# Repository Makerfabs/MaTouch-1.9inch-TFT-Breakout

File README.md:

MaTouch 1.9“ TFT Breakout

```c++
/*
Version:		V1.1
Author:		Charlin
Create Date:	2023/8/14
Note:

*/
```

# Makerfabs

[Makerfabs home page](https://www.makerfabs.com/)

[Makerfabs Wiki](https://wiki.makerfabs.com/)

## Intruduce

Product Link:[MaTouch 1.9“ TFT Breakout](https://www.makerfabs.com/MaTouch-1.9-inch-TFT-Breakout.html)

Wiki Link : 

Makerfabs MaTouch 1.9” has got lots of interests, but we got many feedback that there the ESP32S3 pins should be breakout, for users’ application, so we designed this new board.

Compares to the old version, there main updates are the GPIO all been breakout, users can prototype it more easily with a breadboard, or use it as a “controller” for other boards by inserting it to other boards.

## Features

Specs:
- Controller: ESP32-S3
- Wireless: WiFi& Bluetooth 5.0
- LCD: 1.9", 320x170 resolution, driver ST7789V2
- LCD interface: 8 bit 8080
- Touch Panel Driver: CST816D
- USB: USB Native, Type-C
- Power Supply: USB Type-C 5.0V(4.0V~5.25V); 3.7V Lipo battery
- Button: Flash button and reset button
- MicroSD: Yes
- Arduino support: Yes
- MicroPython support: Yes
- Operation temperature: -40℃ to +85℃

# Usage

## Libraries

Related library versions

- Use type-c use cable connect USB-TTL to PC.
- Select "ESP32-S3 DEV Module"
- Select PSRAM "OPI PSRAM"

"mf_Lvgl" library is modified from Lvgl library (version 8.3.2). 

Please unzip "lib/mf_Lvgl.zip"."TouchLib" and copy to arduino library directory.

## Example

### firmware

Factory test program

### squareline_demo

SquareLine demo, connected DHT11 sensor, button, LED.

[Youtube](https://www.youtube.com/watch?v=VayIuLey8po&t=3s)

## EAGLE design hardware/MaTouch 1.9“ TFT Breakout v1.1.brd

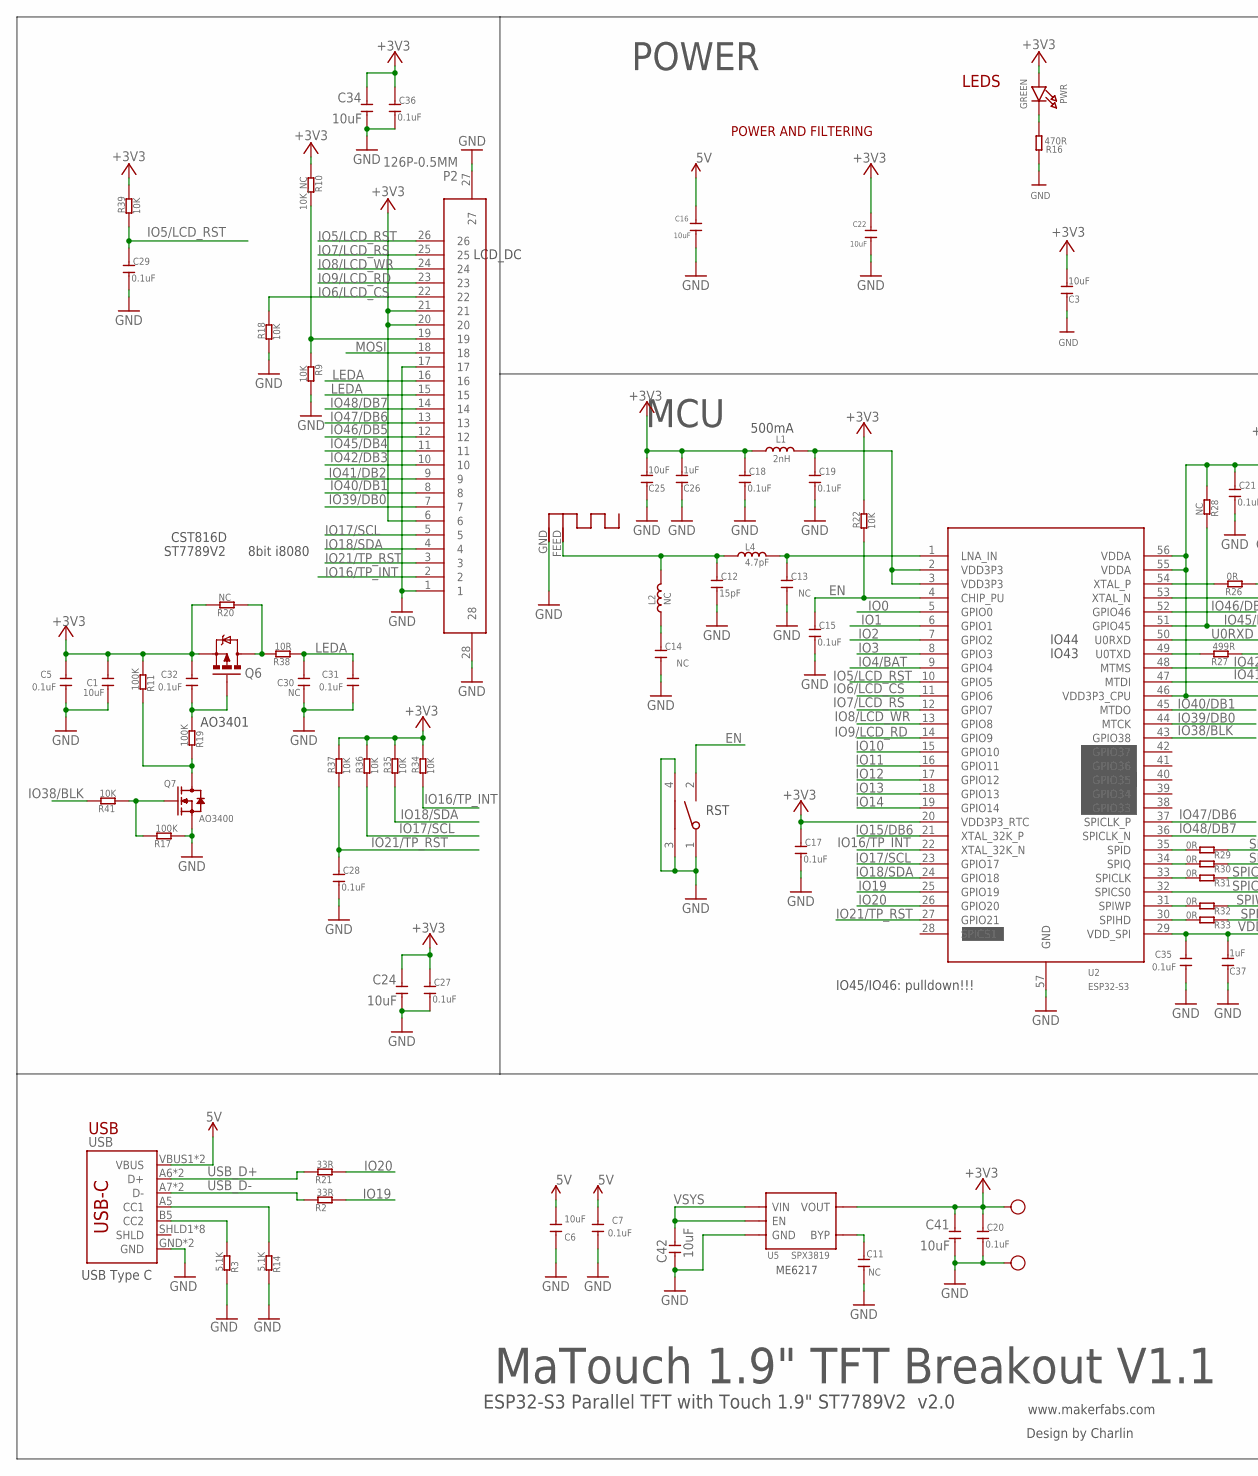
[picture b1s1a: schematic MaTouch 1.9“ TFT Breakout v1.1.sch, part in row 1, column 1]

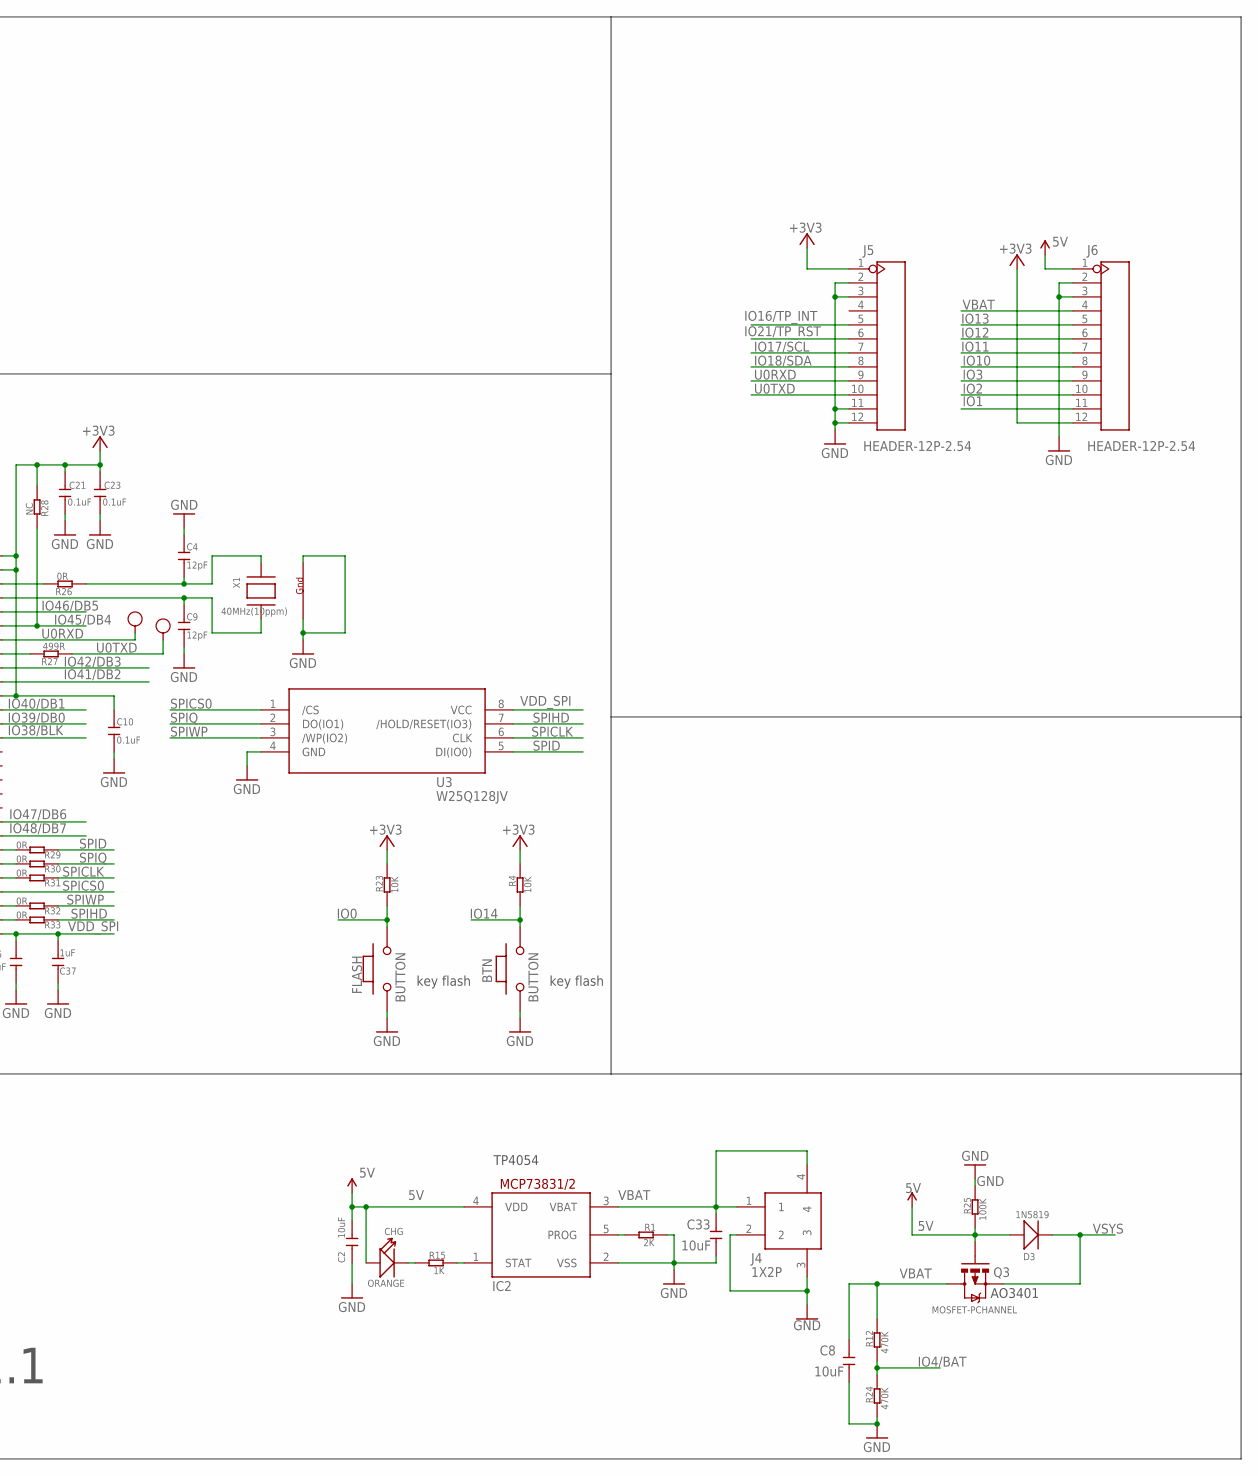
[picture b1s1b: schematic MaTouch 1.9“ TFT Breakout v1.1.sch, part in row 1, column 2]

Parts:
ANT1: ANTENNA; RN-ANT
BTN: BUTTON; 157SW
C1, C2, C8, C16, C22, C24, C33, C34, C41, C42: 10uF; 0603
C3, C6, C25: 10uF; DISCRETE_C0603
C4, C9: 12pF; DISCRETE_C0402
C5, C7, C10, C15, C17, C18, C19, C20, C21, C23, C27, C28, C29, C31, C32, C35, C36: 0.1uF; DISCRETE_C0402
C11, C13, C14: NC; DISCRETE_C0402
C12: 15pF; DISCRETE_C0402
C26, C37: 1uF; DISCRETE_C0603
C30: NC; 0603
CHG: ORANGE; D0603
D3: 1N5819; SOD323
FLASH: BUTTON; 157SW
G: TEST-POINT'4545'; TP-D45MIL; PARTNO DNP
IC2: MCP73831/OT; SOT23-5L
J4: 1X2P; 1X2P-SMT1.25MM
J5, J6: HEADER-12P-2.54; 12P-2.54
L1: 2nH; DISCRETE_L0603
L2: NC; DISCRETE_L0402
L4: 4.7pF; DISCRETE_L0402
P2: 126P-0.5MM; 1*26P-SMT0.5MM
PWR: GREEN; CHIPLED_0805_NOOUTLINE
Q3, Q6: MOSFET-PCHANNEL; SOT23-3
Q7: AO3400; DISCRETE_SOT23
R1: 2K; DISCRETE_R0402
R2, R21: 33R; DISCRETE_R0402
R3, R14: 5.1K; DISCRETE_R0402
R4, R9, R18, R22, R23, R34, R35, R36, R37, R39, R41: 10K; DISCRETE_R0402
R10: 10K_NC; DISCRETE_R0402
R11, R17, R19, R25: 100K; DISCRETE_R0402
R12, R24: 470K; DISCRETE_R0402
R15: 1K; DISCRETE_R0402
R16: 470R; DISCRETE_R0402
R20, R28: NC; DISCRETE_R0402
R26, R29, R30, R31, R32, R33: 0R; DISCRETE_R0402
R27: 499R; DISCRETE_R0402
R38: 10R; DISCRETE_R0402
RST: TS24CA; 2*4*3.5MM
RX: TEST-POINT'4545'; TP-D45MIL; PARTNO DNP
TX: TEST-POINT'4545'; TP-D45MIL; PARTNO DNP
U2: ESP32-S3; QFN56-7*7MM
U3: W25Q128JV; SOIC-8-208MIL
U5: SPX3819; SOT23-5
USB: USB_C5; USB-C-16P-5
V: TEST-POINT'4545'; TP-D45MIL; PARTNO DNP
X1: 40MHz(10ppm); NX3225

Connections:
5V: C2.2, C6.2, C7.2, C16.1, CHG.+, D3.+, IC2.4 (VDD), J6.1, Q3.1 (G), R25.1, USB.VBUS1 (VBUS), USB.VBUS2 (VBUS)
+3V3: C1.2, C3.2, C5.2, C10.2, C17.2, C18.2, C20.2, C21.2, C22.1, C23.2, C24.2, C25.2, C26.2, C27.2, C32.2, C34.2, C36.2, C41.2, J5.1, J6.12, L1.1, P2.6, P2.20, P2.21, PWR.A, Q6.2 (S), R4.2, R10.2, R11.1, R20.2, R22.2, R23.2, R28.1, R34.2, R35.2, R36.2, R37.2, R39.2, U2.20 (VDD3P3_RTC), U2.46 (VDD3P3_CPU), U2.55 (VDDA), U2.56 (VDDA), U5.5 (VOUT), V.T
EN: C15.2, R22.1, RST.2, U2.4 (CHIP_PU)
GND: ANT1.GND, BTN.1, C1.1, C2.1, C3.1, C4.2, C5.1, C6.1, C7.1, C8.1, C9.1, C10.1, C11.1, C12.1, C13.1, C14.1, C15.1, C16.2, C17.1, C18.1, C19.1, C20.1, C21.1, C22.2, C23.1, C24.1, C25.1, C26.1, C27.1, C28.1, C29.1, C30.1, C31.1, C33.1, C34.1, C35.1, C36.1, C37.1, C41.1, C42.1, FLASH.1, G.T, IC2.2 (VSS), J4.2, J4.3, J5.2, J5.3, J5.11, J5.12, J6.2, J6.3, P2.1, P2.17, P2.27, P2.28, Q7.2 (S), R1.2, R3.2, R9.1, R14.2, R16.1, R17.1, R18.1, R24.1, R25.2, RST.1, RST.3, RST.4, U2.57 (GND), U3.4 (GND), U5.2 (GND), USB.GND, USB.GND2 (GND), X1.2 (G2), X1.4 (G1)
IO0: FLASH.2, R23.1, U2.5 (GPIO0)
IO1: J6.11, U2.6 (GPIO1)
IO2: J6.10, U2.7 (GPIO2)
IO3: J6.9, U2.8 (GPIO3)
IO4/BAT: R12.1, R24.2, U2.9 (GPIO4)
IO5/LCD_RST: C29.2, P2.26, R39.1, U2.10 (GPIO5)
IO6/LCD_CS: P2.22, R18.2, U2.11 (GPIO6)
IO7/LCD_RS: P2.25, U2.12 (GPIO7)
IO8/LCD_WR: P2.24, U2.13 (GPIO8)
IO9/LCD_RD: P2.23, U2.14 (GPIO9)
IO10: J6.8, U2.15 (GPIO10)
IO11: J6.7, U2.16 (GPIO11)
IO12: J6.6, U2.17 (GPIO12)
IO13: J6.5, U2.18 (GPIO13)
IO14: BTN.2, R4.1, U2.19 (GPIO14)
IO15/DB6: U2.21 (XTAL_32K_P)
IO16/TP_INT: J5.5, P2.2, R34.1, U2.22 (XTAL_32K_N)
IO17/SCL: J5.7, P2.5, R36.1, U2.23 (GPIO17)
IO18/SDA: J5.8, P2.4, R35.1, U2.24 (GPIO18)
IO19: R2.1, U2.25 (GPIO19)
IO20: R21.1, U2.26 (GPIO20)
IO21/TP_RST: C28.2, J5.6, P2.3, R37.1, U2.27 (GPIO21)
IO38/BLK: R41.2, U2.43 (GPIO38)
IO39/DB0: P2.7, U2.44 (MTCK)
IO40/DB1: P2.8, U2.45 (MTDO)
IO41/DB2: P2.9, U2.47 (MTDI)
IO42/DB3: P2.10, U2.48 (MTMS)
IO45/DB4: P2.11, R28.2, U2.51 (GPIO45)
IO46/DB5: P2.12, U2.52 (GPIO46)
IO47/DB6: P2.13, U2.37 (SPICLK_P)
IO48/DB7: P2.14, U2.36 (SPICLK_N)
LEDA: C30.2, C31.2, P2.15, P2.16, R38.1
MOSI: P2.18
unnamed: IC2.5 (PROG), R1.1
unnamed: C32.1, Q6.1 (G), R19.1
unnamed: R14.1, USB.A5 (CC1)
unnamed: PWR.C, R16.2
unnamed: P2.19, R9.2, R10.1
unnamed: Q6.3 (D), R20.1, R38.2
unnamed: R3.1, USB.B5 (CC2)
unnamed: Q7.3 (D), R11.2, R19.2
unnamed: Q7.1 (G), R17.2, R41.1
unnamed: CHG.-, R15.1
unnamed: IC2.1 (STAT), R15.2
unnamed: ANT1.FEED, C12.2, L2.2, L4.1
unnamed: C13.2, L4.2, U2.1 (LNA_IN)
unnamed: R29.2, U2.35 (SPID)
unnamed: C19.2, L1.2, U2.2 (VDD3P3), U2.3 (VDD3P3)
unnamed: C14.2, L2.1
unnamed: R30.2, U2.34 (SPIQ)
unnamed: R26.2, U2.54 (XTAL_P)
unnamed: R31.2, U2.33 (SPICLK)
unnamed: R32.2, U2.31 (SPIWP)
unnamed: R33.2, U2.30 (SPIHD)
unnamed: R27.2, U2.49 (U0TXD)
unnamed: C9.2, U2.53 (XTAL_N), X1.3 (X2)
unnamed: C4.1, R26.1, X1.1 (X1)
unnamed: C11.2, U5.4 (BYP)
SPICLK: R31.1, U3.6 (CLK)
SPICS0: U2.32 (SPICS0), U3.1 (/CS)
SPID: R29.1, U3.5 (DI(IO0))
SPIHD: R33.1, U3.7 (/HOLD/RESET(IO3))
SPIQ: R30.1, U3.2 (DO(IO1))
SPIWP: R32.1, U3.3 (/WP(IO2))
U0RXD: J5.9, RX.T, U2.50 (U0RXD)
U0TXD: J5.10, R27.1, TX.T
USB_D+: R21.2, USB.A6 (D+), USB.B6 (D+)
USB_D-: R2.2, USB.A7 (D-), USB.B7 (D-)
VBAT: C8.2, C33.2, IC2.3 (VBAT), J4.1, J4.4, J6.4, Q3.3 (D), R12.2
VDD_SPI: C35.2, C37.2, U2.29 (VDD_SPI), U3.8 (VCC)
VSYS: C42.2, D3.-, Q3.2 (S), U5.1 (VIN), U5.3 (EN)

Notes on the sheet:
www.makerfabs.com
Design by Charlin
LEDS
POWER AND FILTERING
key flash
ESP32-S3 Parallel TFT with Touch 1.9" ST7789V2 v2.0
POWER
USB
USB Type C
MCU
500mA
ME6217
TP4054
AO3401
8bit i8080
IO45/IO46: pulldown!!!
IO43
IO44
CST816D
ST7789V2
LCD_DC
RST
MaTouch 1.9" TFT Breakout V1.1

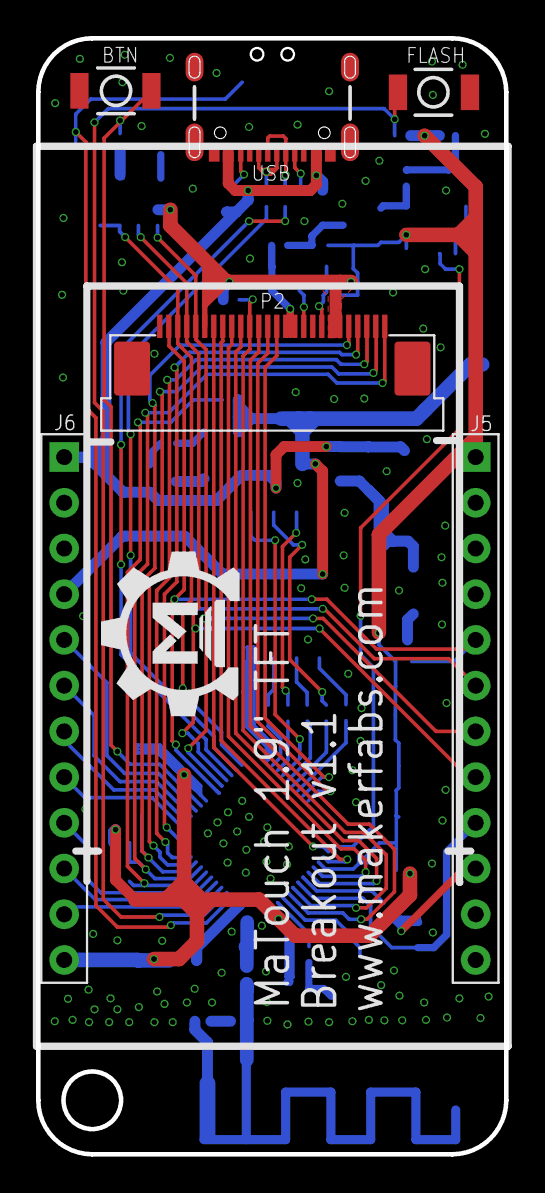
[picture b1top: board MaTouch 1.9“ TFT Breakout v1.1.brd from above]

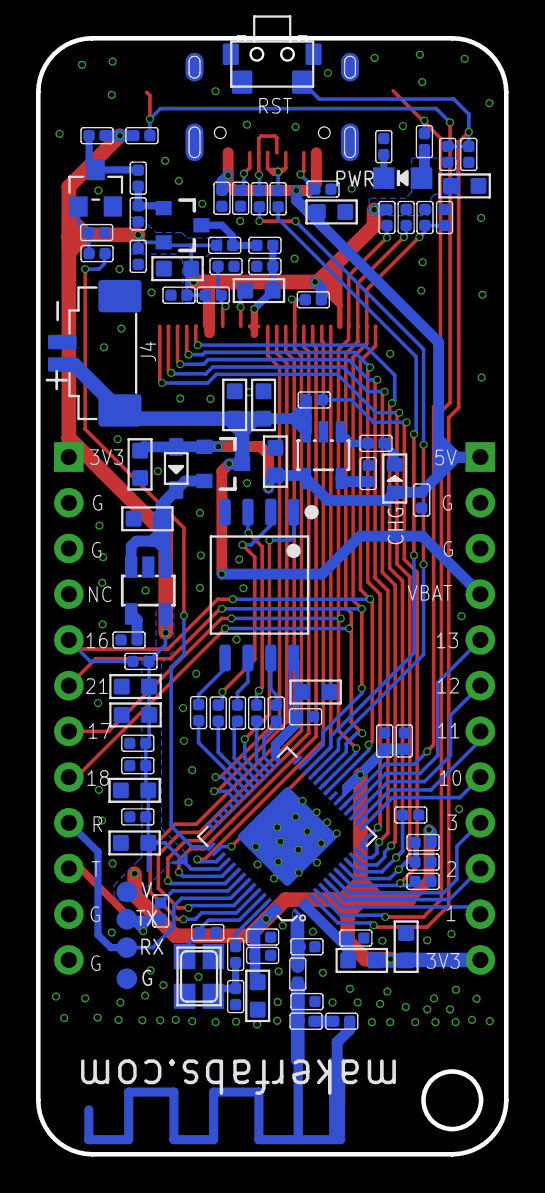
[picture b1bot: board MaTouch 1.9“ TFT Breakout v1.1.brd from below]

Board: 2 copper layers, 26.0 x 62.0 mm, 102 parts (95 on the bottom side), 73 nets.

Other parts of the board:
U$1: MAKERFABS_0.3

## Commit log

2023-08-14 The hardware and default code
2023-08-17 Add squareline demo
2023-08-22 Edit readme
2024-04-10 Add laser ranging demo

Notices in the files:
parts and their libraries:
microbuilder: This work is placed in the public domain, and may be freely used for commercial and non-commercial work with the following conditions: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
User-Submitted: Licensing: Creative Commons ShareAlike 4.0 International - https://creativecommons.org/licenses/by-sa/4.0
